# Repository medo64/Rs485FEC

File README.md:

[RS-485 Framework Expansion Card](https://medo64.com/rs485framecard/)
=====================================================================

This Framework laptop expansion card will show up on your system as a serial
device and allow for non-isolated RS-485 communication up to 3,000,800 baud
rate.

Please note that this card is using automatic transmit control and is 120Ω
terminated.

## Pinout

To connect to this board, one has to use a 4-pin JST XH connector. The following
table represents the pinout, pin 1 being on the left as looking into the
expansion card.

| # | Ref | Description                                     |
|--:|-----|-------------------------------------------------|
| 1 | GND | Ground connection                               |
| 2 | A   | Negative (low for logic 1 and high for logic 0) |
| 3 | B   | Positive (high for logic 1 and low for logic 0) |
| 4 | 5V  | 100 mA power supply                             |

As power consumption is low, wires can be almost any AWG. I would recommend
using 24 AWG wire 0.25 mm² as they allow for greater compatibility with other
connectors.

## Supported Speeds

This board employs the FT232R as its UART chip, and consequently, it supports
all the baud rates this chip [can handle](https://ftdichip.com/Documents/AppNotes/AN232B-05_BaudRates.pdf)
up to 500,000 baud which is the limit of isolator chip used. The table below
lists the standard baud rates.

| Baud rate |    Actual | Error |    Divisor |
|----------:|----------:|------:|-----------:|
|       300 |       300 | 0.00% |  10000.000 |
|       600 |       600 | 0.00% |   5000.000 |
|     1,200 |     1,200 | 0.00% |   2500.000 |
|     1,800 |     1,800 | 0.00% |   1666.625 |
|     2,400 |     2,400 | 0.00% |   1250.000 |
|     4,800 |     4,800 | 0.00% |    625.000 |
|     7,200 |     7,201 | 0.01% |    416.625 |
|     9,600 |     9,600 | 0.00% |    312.500 |
|    14,400 |    14,406 | 0.04% |    208.250 |
|    19,200 |    19,200 | 0.00% |    156.250 |
|    28,800 |    28,812 | 0.04% |    104.125 |
|    38,400 |    38,400 | 0.00% |     78.125 |
|    57,600 |    57,692 | 0.16% |     52.000 |
|   115,200 |   115,385 | 0.16% |     26.000 |
|   230,400 |   230,769 | 0.16% |     13.000 |
|   460,800 |   461,538 | 0.16% |      6.500 |
|   921,600 |   923,077 | 0.16% |      3.250 |
| 1,000,000 | 1,000,000 | 0.00% |      3.000 |
| 2,000,000 | 2,000,000 | 0.00% |      2.000 |
| 3,000,000 | 3,000,000 | 0.00% |      0.000 |

While rates above this can be set, they are not guaranteed to work.

---
*You can check my blog and other projects at [www.medo64.com](https://www.medo64.com/electronics/).*

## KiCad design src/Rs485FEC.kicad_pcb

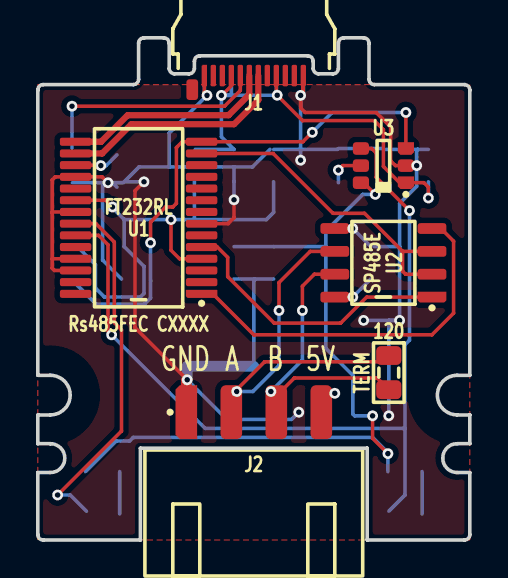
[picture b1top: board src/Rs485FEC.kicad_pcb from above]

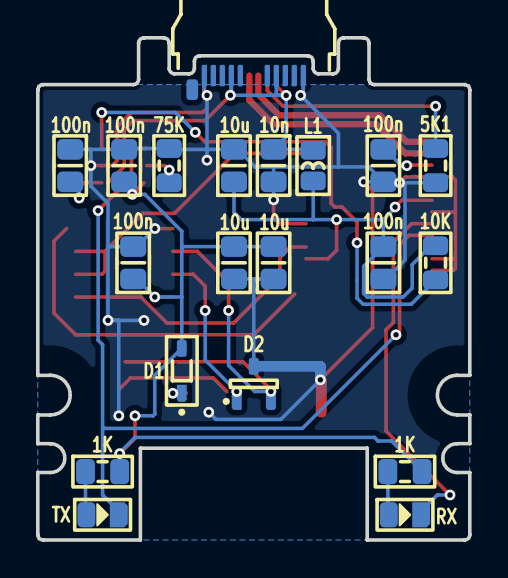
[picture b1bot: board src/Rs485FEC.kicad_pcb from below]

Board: 2 copper layers, 24.0 x 27.9 mm, 25 parts (19 on the bottom side), 20 nets.

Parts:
C1: 10n; C (0805)
C2, C3, C4, C5, C6: 100n; C (0805)
C7, C8, C9: 10u; C (0805)
D1: CUS08F30; D (SOD323)
D2: SM12T1G; D TVS 7-12V [SM712] (SOT23-3)
DS1: RX; DS (0805)
DS2: TX; DS (0805)
J1: 105444-0001; J USB C 3.2 Edge (24w)
J2: B4B-XH-A; J JST XH Edge [RS485] (4w)
L1: 600R; L (0805)
R1: 120; R (0805)
R2, R3: 1K; R (0805)
R5: 5K1; R (0805)
R5#2: 10K; R (0805)
R6: 75K; R (0805)
U1: FT232RL; U Transceiver UART [FT232R] (SSOP-28)
U2: SP485E; U Transciever RS485 [SP485EEN] (SOIC-8)
U3: AP22652; U LoadSwitch Adjustable [AP22652W6-7] (SOT23-6)

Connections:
3V3_UART_USB: C3.2, U1.17
5V: C2.2, C7.2, L1.1, R5#2.1, U1.4, U1.20
5V_OUT: D1.1, J2.4
5V_SWITCHED: C4.2, C6.1, C8.1, C9.1, D1.2, R2.1, R3.1, U2.8, U3.6
5V_USB: C1.2, C5.1, J1.A4, J1.A9, J1.B04, J1.B09, L1.2, U3.1
A: D2.2, J2.2, R1.1, U2.6
A_CC: J1.A5, R5.2
B: D2.1, J2.3, R1.2, U2.7
GND: C1.1, C2.1, C3.1, C4.1, C5.2, C6.2, C7.1, C8.2, C9.2, D2.3, J1.A1, J1.A12, J1.B01, J1.B12, J2.1, R5.1, R6.2, U1.7, U1.18, U1.21, U1.25, U1.26, U2.5, U3.2
ILIMIT: R6.1, U3.5
LED_RXD: DS1.1, U1.22
LED_RXD': DS1.2, R2.2
LED_TXD: DS2.1, U1.23, U3.4
LED_TXD': DS2.2, R3.2
PWREN#: R5#2.2, U1.14, U3.3
RXD: U1.5, U2.1
TXD: U1.1, U2.4
TXDEN: U1.13, U2.2, U2.3
USB_DM: J1.A7, U1.16
USB_DP: J1.A6, U1.15

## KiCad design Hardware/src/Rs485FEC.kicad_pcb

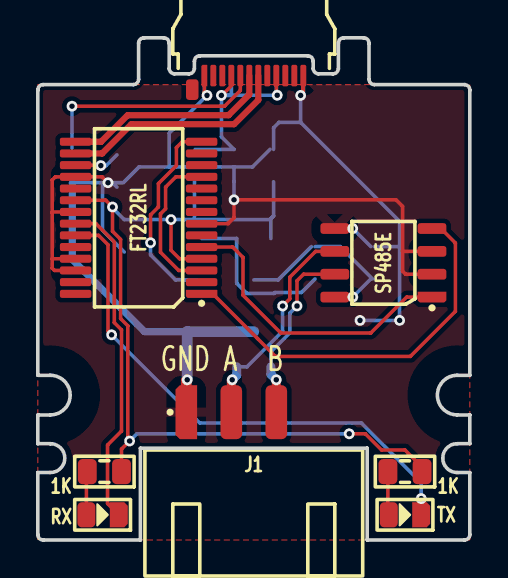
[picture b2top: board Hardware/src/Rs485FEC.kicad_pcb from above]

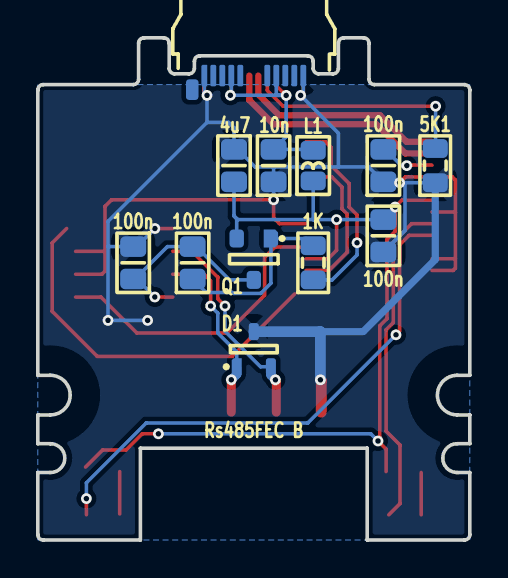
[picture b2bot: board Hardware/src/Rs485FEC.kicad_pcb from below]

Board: 2 copper layers, 24.0 x 27.9 mm, 19 parts (11 on the bottom side), 19 nets.

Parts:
C1: 10n; C (0805)
C2, C3, C4, C5: 100n; C (0805)
C11: 4u7; C (0805)
D1: SM12T1G; D TVS SM05T1G (SOT23-3)
DS1: RX; DS (0805)
DS2: TX; DS (0805)
J1: B3B-XH-A; J JST XH Edge [RS485] (4w)
L1: 600R; L (0805)
P1: 105444-0001; P USB C 3.2 Edge (24w)
Q1: DMP3099L-13; Q MOSFET-P (SOT23-3)
R1, R2, R3: 1K; R (0805)
R4: 5K1; R (0805)
U1: FT232RL; U Transciever UART FT232RL (SSOP-28)
U2: SP485E; U Transciever RS485 SP485E (SOIC-8)

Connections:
3V3: C3.2, U1.17
5V: C2.2, C11.2, L1.1, Q1.2, R1.1, R2.1, U1.4, U1.20
5V_SW: C4.2, C5.2, Q1.3, U2.8
A: D1.2, J1.2, U2.6
A_CC: P1.A5, R4.2
B: D1.1, J1.3, U2.7
GND: C1.1, C2.1, C3.1, C4.1, C11.1, D1.3, J1.1, P1.A1, P1.A12, P1.B01, P1.B12, R4.1, U1.7, U1.18, U1.21, U1.25, U1.26, U2.2, U2.3, U2.5
LED_RXD: DS1.1, U1.22
LED_RXD': DS1.2, R1.2
LED_TXD: DS2.1, U1.23
LED_TXD': DS2.2, R2.2
PWREN#: R3.1, U1.14
PWREN#': C5.1, Q1.1, R3.2
RTS_CTS: U1.3, U1.11
RXD: U1.5, U2.1
TXD: U1.1, U2.4
USB_DM: P1.A7, U1.16
USB_DP: P1.A6, U1.15
USB_Vin: C1.2, L1.2, P1.A4, P1.A9, P1.B04, P1.B09

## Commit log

2022-08-22 Move diodes a bit
2022-08-22 Fixed zener diode
2022-08-26 Added optional SOT23 protection zener
2022-08-26 Replacing individual zeners with SOT23 zeners
2022-09-18 Minor refactorings
2022-10-08 Added FTDI variant
2022-10-08 Added power saving circuit to FTDI variant
2022-10-08 Added extra capacitor
2022-11-07 USB VID/PID allocation
2022-11-07 Initial firmware (not working)
2023-11-04 Updated for KiCAD version
2023-11-04 Added RTS/CTS loopback
2023-11-12 Refactoring directories
2023-11-12 Fixed TXDEN signal
2023-11-12 Updating readme files
2023-11-12 Added back fail-safe biased termination
2023-11-13 Removed fail-safe termination
2023-11-13 Moving LEDs to bottom
2023-11-13 Moved termination resistor
2023-12-26 Added PWREN pullup and moved LED 5V to switched
2023-12-26 Removed internal RTS/CTS connection
2023-12-29 Updated connector to solder all 4 pins
2023-12-30 Refactoring copper pour
2024-01-31 Moved board RefDes to top
2024-04-02 Updated connector designators
2024-06-10 Updated for KiCAD 8
2024-06-10 Added current limiting
2025-01-26 Fixed refdes
2025-01-26 Updated text
2025-02-02 Fixed pinout
